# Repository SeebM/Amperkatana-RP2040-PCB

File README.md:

# Modification 08/2025
This PCB is based on the template below and should - once it is finished - fit into a Ampersand keyboard case and compatible other cases like dizzyskizzos Amperconcrete.

# Keyboard PCB Integration with Microcontrollers

This GitHub project provides guidance on integrating microcontrollers into keyboard PCBs. It focuses on the RP2040 microcontroller from the Raspberry Pi foundation, which offers several features such as a dual-core Arm Cortex-M0+ processor, multiple communication interfaces, and QMK/Via/Vial support.

## Schematic Capture

Before proceeding with board layout, it is important to understand the steps involved in schematic capture. The README provides an overview of the RP2040 microcontroller, including its integrated 3.3V->1.1V regulator, pin connections like TESTEN and RUN_, and the need for additional components such as decoupling capacitors.

## Power Supply and USB Bootloader

The RP2040 is powered through USB and features a built-in USB bootloader for easy programming. The README mentions the use of a 3.3V fixed regulator, USBLC6 ESD protection IC, PTC resettable fuse, and a ferrite bead for EMI suppression.

## PCB Connectors

The project includes information about the USB-C port, its orientation detection pins (CC1/CC2), and the 5.1k resistors used for USB power delivery. Additionally, a JST connector is introduced for use with a Unified Daughter Board.

## Crystal and External Flash

A crystal is employed to provide accurate timing for USB functionality. The README also covers the connections to the RP2040's external flash, including buttons for forcing the ROM bootloader and resetting the microcontroller.

## Indicator LED and Switch Matrix

An indicator LED example for caps lock indication is given, along with considerations for selecting an appropriate LED resistor value. The README highlights the use of diodes in the switch matrix to prevent "ghosting" and enable n-key rollover.

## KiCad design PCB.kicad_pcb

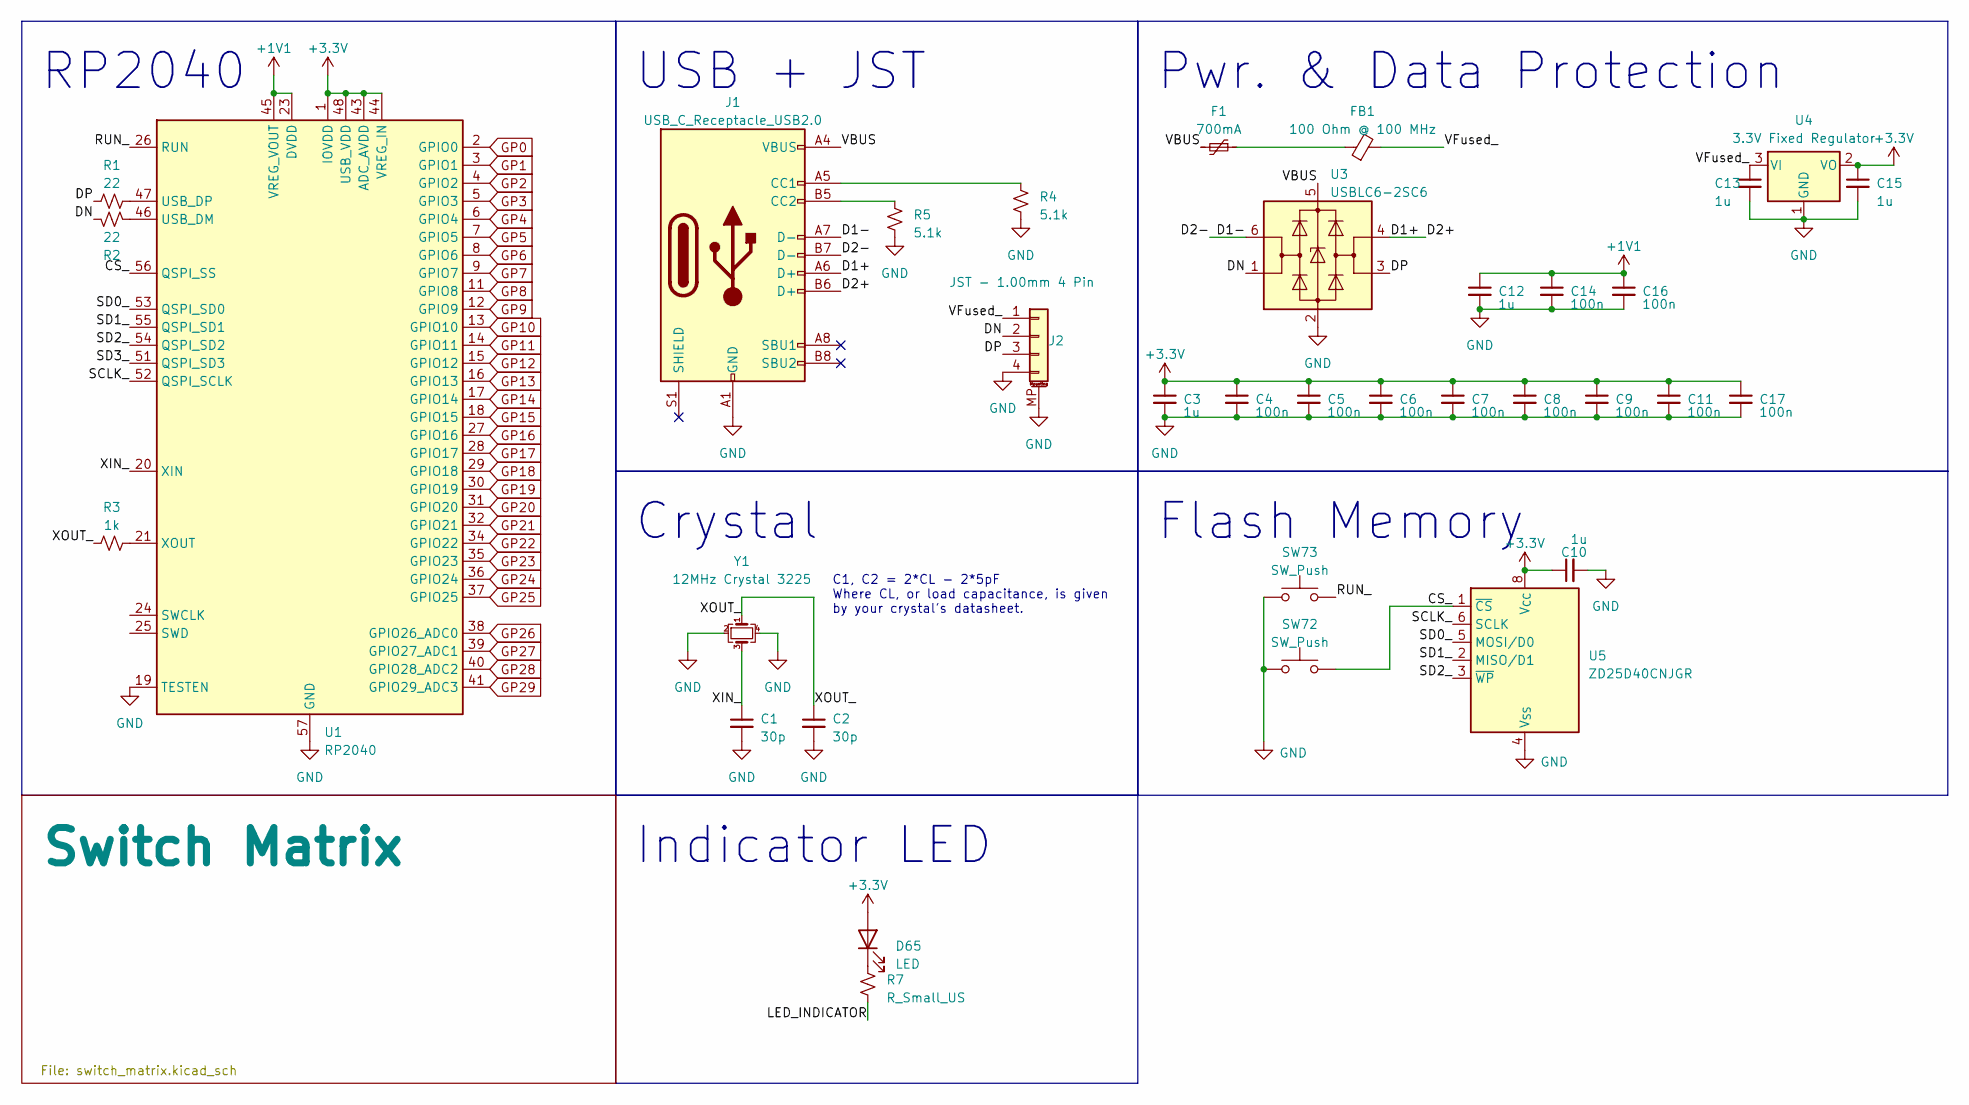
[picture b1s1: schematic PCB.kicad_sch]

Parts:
C1, C2: 30p; C_0402_1005Metric; LCSC C1562
C3, C10, C12, C13, C15: 1u; C_0402_1005Metric; LCSC C52923
C4, C5, C6, C7, C8, C9, C11, C14, C16, C17: 100n; C_0402_1005Metric; LCSC C1525
D65: LED; LED_MX_3mm
F1: 700mA; Fuse_0402_1005Metric; LCSC C914086
FB1: 100 Ohm @ 100 MHz; L_0402_1005Metric; LCSC C85812
J1: USB_C_Receptacle_USB2.0; USB_C_Receptacle_GCT_USB4085
J2: JST - 1.00mm 4 Pin; JST_SH_SM04B-SRSS-TB_1x04-1MP_P1.00mm_Horizontal; LCSC C160404
R1, R2: 22; R_0402_1005Metric; LCSC C25152
R3: 1k; R_0402_1005Metric; LCSC C106235
R4, R5: 5.1k; R_0402_1005Metric; LCSC C25905
R7: R_Small_US; R_0402_1005Metric
SW72, SW73: SW_Push; SW_SPST_SKQG_WithoutStem; LCSC C115351
U1: RP2040; QFN-56-1EP_7x7mm_P0.4mm_EP3.2x3.2mm_ThermalVias; LCSC C2040
U3: USBLC6-2SC6; SOT-23-6; LCSC C558442
U4: 3.3V Fixed Regulator; TSOT-23; LCSC C150715
U5: ZD25D40CNJGR; USON-8_1.5x1.5mm_P0.45mm; LCSC C3646778
Y1: 12MHz Crystal 3225; Crystal_SMD_3225-4Pin_3.2x2.5mm; LCSC C9002

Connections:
+1V1: C12.1, C14.1, C16.1, U1.23 (DVDD), U1.45 (VREG_VOUT), U1.50 (DVDD)
+3.3V: C3.1, C4.1, C5.1, C6.1, C7.1, C8.1, C9.1, C10.1, C11.1, C15.1, C17.1, D65.2 (A), U1.1 (IOVDD), U1.10 (IOVDD), U1.22 (IOVDD), U1.33 (IOVDD), U1.42 (IOVDD), U1.43 (ADC_AVDD), U1.44 (VREG_IN), U1.48 (USB_VDD), U1.49 (IOVDD), U4.2 (VO), U5.8 (V_{CC})
/CS_: SW72.2, U1.56 (QSPI_SS), U5.1 (~CS)
/D1+: J1.A6 (D+), J1.B6 (D+), U3.4 (I/O2)
/D1-: J1.A7 (D-), J1.B7 (D-), U3.6 (I/O1)
/DN: J2.2, R2.2, U3.1 (I/O1)
/DP: J2.3, R1.1, U3.3 (I/O2)
/LED_INDICATOR: R7.2
/RUN_: SW73.2, U1.26 (RUN)
/SCLK_: U1.52 (QSPI_SCLK), U5.6 (SCLK)
/SD0_: U1.53 (QSPI_SD0), U5.5 (MOSI/D0)
/SD1_: U1.55 (QSPI_SD1), U5.2 (MISO/D1)
/SD2_: U1.54 (QSPI_SD2), U5.3 (~WP)
/SD3_: U1.51 (QSPI_SD3)
/VBUS: F1.2, J1.A4 (VBUS), J1.A9 (VBUS), J1.B4 (VBUS), J1.B9 (VBUS), U3.5 (VBUS)
/VFused_: C13.1, FB1.2, J2.1, U4.3 (VI)
/XIN_: C1.1, U1.20 (XIN), Y1.3
/XOUT_: C2.1, R3.1, Y1.1
Col0: U1.2 (GPIO0); also elsewhere on the board
Col1: U1.3 (GPIO1); also elsewhere on the board
Col2: U1.4 (GPIO2); also elsewhere on the board
Col3: U1.5 (GPIO3); also elsewhere on the board
Col4: U1.6 (GPIO4); also elsewhere on the board
Col5: U1.7 (GPIO5); also elsewhere on the board
Col6: U1.8 (GPIO6); also elsewhere on the board
Col7: U1.9 (GPIO7); also elsewhere on the board
Col8: U1.11 (GPIO8); also elsewhere on the board
Col9: U1.12 (GPIO9); also elsewhere on the board
Col10: U1.13 (GPIO10); also elsewhere on the board
Col11: U1.14 (GPIO11); also elsewhere on the board
Col12: U1.15 (GPIO12); also elsewhere on the board
GND: C1.2, C2.2, C3.2, C4.2, C5.2, C6.2, C7.2, C8.2, C9.2, C10.2, C11.2, C12.2, C13.2, C14.2, C15.2, C16.2, C17.2, J1.A1 (GND), J1.A12 (GND), J1.B1 (GND), J1.B12 (GND), J2.4, J2.MP (MountPin), R4.1, R5.1, SW72.1, SW73.1, U1.19 (TESTEN), U1.57 (GND), U3.2 (GND), U4.1 (GND), U5.4 (V_{SS}), U5.9 (PAD/V_{SS}), Y1.2, Y1.4
GP13: U1.16 (GPIO13)
GP14: U1.17 (GPIO14); also elsewhere on the board
GP15: U1.18 (GPIO15); also elsewhere on the board
GP16: U1.27 (GPIO16); also elsewhere on the board
GP17: U1.28 (GPIO17); also elsewhere on the board
GP18: U1.29 (GPIO18)
GP19: U1.30 (GPIO19)
GP20: U1.31 (GPIO20)
GP21: U1.32 (GPIO21)
GP22: U1.34 (GPIO22)
GP23: U1.35 (GPIO23)
GP24: U1.36 (GPIO24)
GP25: U1.37 (GPIO25)
GP26: U1.38 (GPIO26_ADC0)
GP27: U1.39 (GPIO27_ADC1)
GP28: U1.40 (GPIO28_ADC2)
GP29: U1.41 (GPIO29_ADC3)
unnamed: D65.1 (K), R7.1
unnamed: F1.1, FB1.1
unnamed: J1.A5 (CC1), R4.2
unnamed: J1.B5 (CC2), R5.2
unnamed: R2.1, U1.46 (USB_DM)
unnamed: R1.2, U1.47 (USB_DP)
unnamed: R3.2, U1.21 (XOUT)

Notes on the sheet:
Flash Memory
Pwr. & Data Protection
C1, C2 = 2*CL - 2*5pF Where CL, or load capacitance, is given by your crystal's datasheet.
Indicator LED
Crystal
RP2040
USB + JST

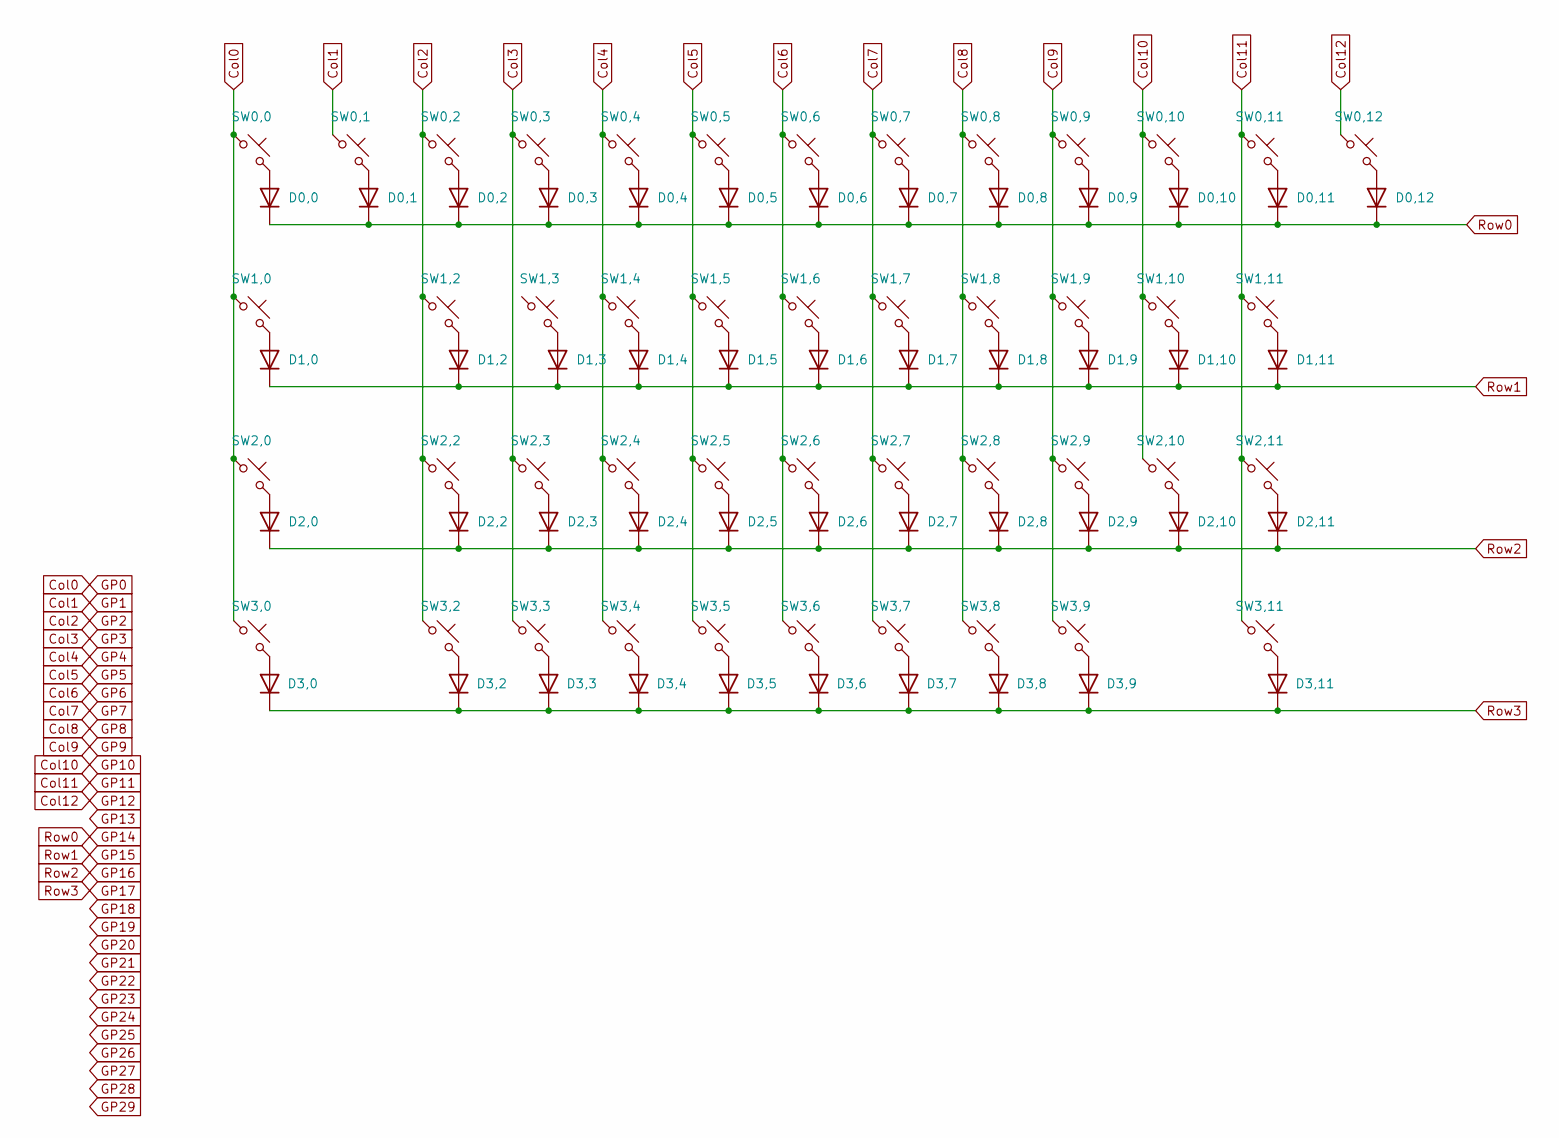
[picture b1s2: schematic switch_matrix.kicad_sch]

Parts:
D0,0, D0,1, D0,2, D0,3, D0,4, D0,5, D0,6, D0,7, D0,8, D0,9, D0,10, D0,11, D0,12, D1,0, D1,2, D1,3, D1,4, D1,5, D1,6, D1,7, D1,8, D1,9, D1,10, D1,11, D2,0, D2,2, D2,3, D2,4, D2,5, D2,6, D2,7, D2,8, D2,9, D2,10, D2,11, D3,0, D3,2, D3,3, D3,4, D3,5, D3,6, D3,7, D3,8, D3,9, D3,11: 1N4148W; D_SOD-123
SW0,0, SW0,1, SW0,2, SW0,3, SW0,4, SW0,5, SW0,6, SW0,7, SW0,8, SW0,9, SW0,10, SW0,11, SW1,2, SW1,3, SW1,4, SW1,5, SW1,6, SW1,7, SW1,8, SW1,9, SW1,10, SW2,2, SW2,3, SW2,4, SW2,5, SW2,6, SW2,7, SW2,8, SW2,9, SW2,10, SW3,0, SW3,2, SW3,3, SW3,6, SW3,11: MX_SW_solder; SW_MX_1u
SW0,12, SW2,0: MX_SW_solder; SW_MX_1.5u
SW1,0: MX_SW_solder; SW_MX_1.75u
SW1,11: MX_SW_solder; STAB_MX_P_2.25u
SW2,11: MX_SW_solder; STAB_MX_P_2u
SW3,4, SW3,7, SW3,8, SW3,9: MX_SW_solder; SW_MX_1.25u
SW3,5: MX_SW_solder; STAB_MX_P_3u

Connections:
Col0: SW0,0.1, SW1,0.1, SW2,0.1, SW3,0.1; also elsewhere on the board
Col1: SW0,1.1; also elsewhere on the board
Col2: SW0,2.1, SW1,2.1, SW2,2.1, SW3,2.1; also elsewhere on the board
Col3: SW0,3.1, SW2,3.1, SW3,3.1; also elsewhere on the board
Col4: SW0,4.1, SW1,4.1, SW2,4.1, SW3,4.1; also elsewhere on the board
Col5: SW0,5.1, SW1,5.1, SW2,5.1, SW3,5.1; also elsewhere on the board
Col6: SW0,6.1, SW1,6.1, SW2,6.1, SW3,6.1; also elsewhere on the board
Col7: SW0,7.1, SW1,7.1, SW2,7.1, SW3,7.1; also elsewhere on the board
Col8: SW0,8.1, SW1,8.1, SW2,8.1, SW3,8.1; also elsewhere on the board
Col9: SW0,9.1, SW1,9.1, SW2,9.1, SW3,9.1; also elsewhere on the board
Col10: SW0,10.1, SW1,10.1, SW2,10.1; also elsewhere on the board
Col11: SW0,11.1, SW1,11.1, SW2,11.1, SW3,11.1; also elsewhere on the board
Col12: SW0,12.1; also elsewhere on the board
GP14: D0,0.1 (K), D0,1.1 (K), D0,2.1 (K), D0,3.1 (K), D0,4.1 (K), D0,5.1 (K), D0,6.1 (K), D0,7.1 (K), D0,8.1 (K), D0,9.1 (K), D0,10.1 (K), D0,11.1 (K), D0,12.1 (K); also elsewhere on the board
GP15: D1,0.1 (K), D1,2.1 (K), D1,3.1 (K), D1,4.1 (K), D1,5.1 (K), D1,6.1 (K), D1,7.1 (K), D1,8.1 (K), D1,9.1 (K), D1,10.1 (K), D1,11.1 (K); also elsewhere on the board
GP16: D2,0.1 (K), D2,2.1 (K), D2,3.1 (K), D2,4.1 (K), D2,5.1 (K), D2,6.1 (K), D2,7.1 (K), D2,8.1 (K), D2,9.1 (K), D2,10.1 (K), D2,11.1 (K); also elsewhere on the board
GP17: D3,0.1 (K), D3,2.1 (K), D3,3.1 (K), D3,4.1 (K), D3,5.1 (K), D3,6.1 (K), D3,7.1 (K), D3,8.1 (K), D3,9.1 (K), D3,11.1 (K); also elsewhere on the board
unnamed: D0,0.2 (A), SW0,0.2
unnamed: D0,1.2 (A), SW0,1.2
unnamed: D0,2.2 (A), SW0,2.2
unnamed: D0,3.2 (A), SW0,3.2
unnamed: D0,4.2 (A), SW0,4.2
unnamed: D0,5.2 (A), SW0,5.2
unnamed: D0,6.2 (A), SW0,6.2
unnamed: D0,7.2 (A), SW0,7.2
unnamed: D0,8.2 (A), SW0,8.2
unnamed: D0,9.2 (A), SW0,9.2
unnamed: D0,10.2 (A), SW0,10.2
unnamed: D0,11.2 (A), SW0,11.2
unnamed: D0,12.2 (A), SW0,12.2
unnamed: D1,0.2 (A), SW1,0.2
unnamed: D1,2.2 (A), SW1,2.2
unnamed: D1,3.2 (A), SW1,3.2
unnamed: D1,4.2 (A), SW1,4.2
unnamed: D1,5.2 (A), SW1,5.2
unnamed: D1,6.2 (A), SW1,6.2
unnamed: D1,7.2 (A), SW1,7.2
unnamed: D1,8.2 (A), SW1,8.2
unnamed: D1,9.2 (A), SW1,9.2
unnamed: D1,10.2 (A), SW1,10.2
unnamed: D1,11.2 (A), SW1,11.2
unnamed: D2,0.2 (A), SW2,0.2
unnamed: D2,2.2 (A), SW2,2.2
unnamed: D2,3.2 (A), SW2,3.2
unnamed: D2,4.2 (A), SW2,4.2
unnamed: D2,5.2 (A), SW2,5.2
unnamed: D2,6.2 (A), SW2,6.2
unnamed: D2,7.2 (A), SW2,7.2
unnamed: D2,8.2 (A), SW2,8.2
unnamed: D2,9.2 (A), SW2,9.2
unnamed: D2,10.2 (A), SW2,10.2
unnamed: D2,11.2 (A), SW2,11.2
unnamed: D3,0.2 (A), SW3,0.2
unnamed: D3,2.2 (A), SW3,2.2
unnamed: D3,3.2 (A), SW3,3.2
unnamed: D3,4.2 (A), SW3,4.2
unnamed: D3,5.2 (A), SW3,5.2
unnamed: D3,6.2 (A), SW3,6.2
unnamed: D3,7.2 (A), SW3,7.2
unnamed: D3,8.2 (A), SW3,8.2
unnamed: D3,9.2 (A), SW3,9.2
unnamed: D3,11.2 (A), SW3,11.2

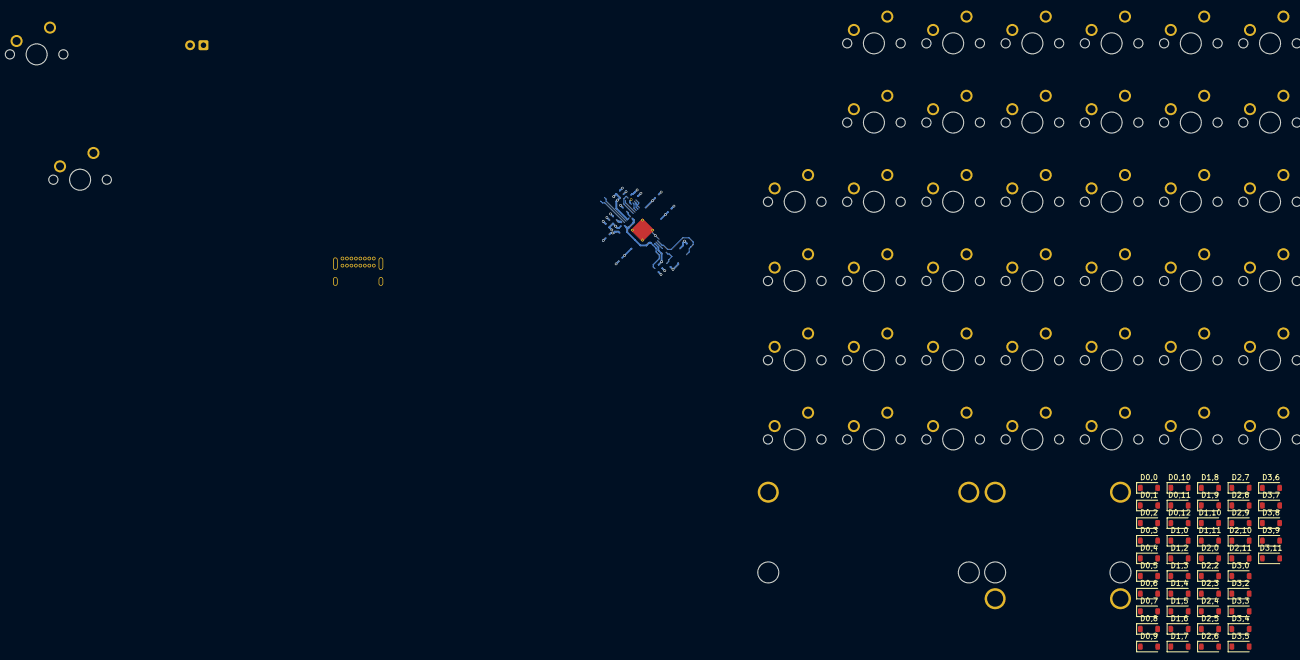
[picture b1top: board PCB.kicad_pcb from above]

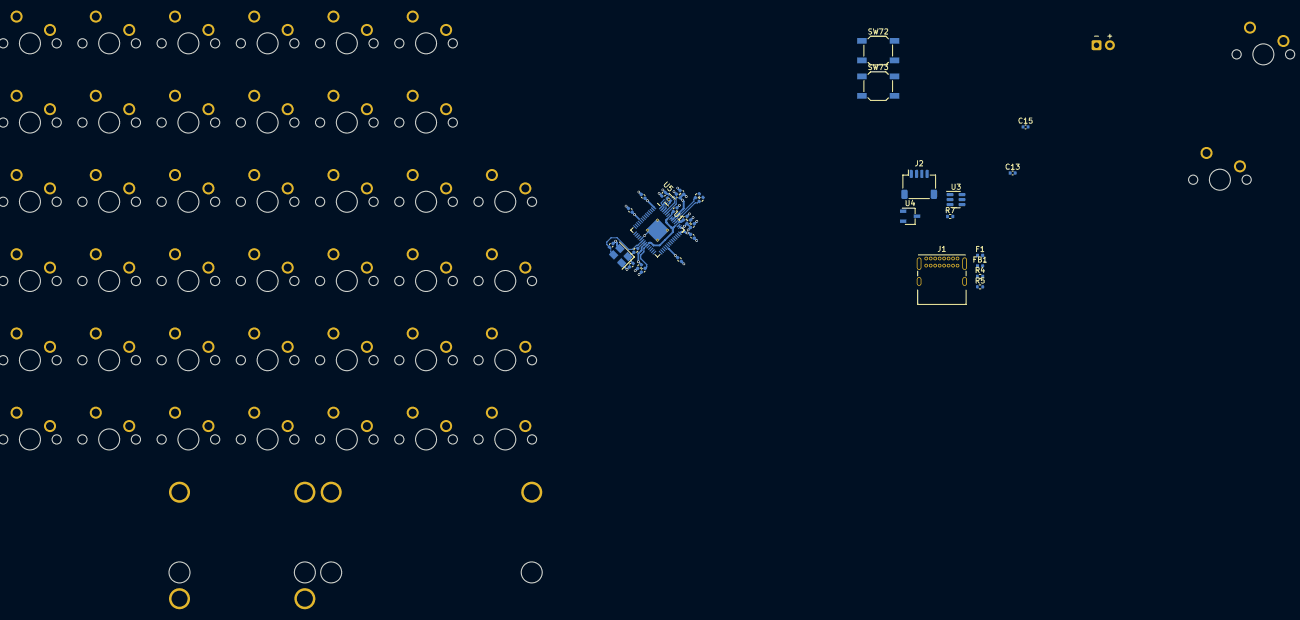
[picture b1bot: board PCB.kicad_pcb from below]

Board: 4 copper layers, 125 parts (34 on the bottom side), 83 nets.

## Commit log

2025-08-08 KLE added
2025-08-08 Update Schematic with keyboard layout
2025-08-08 ignore file locks
2025-08-08 First pcb footprints
